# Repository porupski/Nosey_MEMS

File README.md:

# Nosey MEMS

**/ˈnɔɪzi miːmz/** — a fully open-source nasometer.

Nosey MEMS is a general purpose **mono MEMS microphone preamp**. It was specifically designed for integration with **Nosey** ([GitHub](https://github.com/phoneticslab/nosey) [Paper, IS25](https://www.isca-archive.org/interspeech_2025/dewhurst25_interspeech.pdf)) for acoustic nasalance measurements. A **stereo pair of boards** — one nasal, one oral — in the (not yet) adapted Nosey 3D-printed handle and baffle.

## What you get

- Open **KiCad 10.0** schematic, PCB and JLCPCB production files
- Small 25 × 50 mm board: NA-FFA381-A10-1 MEMS mic, OPA1652 balanced output, +48V phantom via XLR3
- Simple, low-cost (~€20 per built board as of June 2026), low-maintenance design
- Built for general purpose, aimed at phonetics, but the schematic/PCB can be adapted to any use

## Where to look

- **Documentation:** [porupski.github.io/Nosey_MEMS](https://porupski.github.io/Nosey_MEMS/)
- **`KiCad_files/`** — schematic, PCB layout, production `.zip`
- **`REW_files/`** — measured frequency response (Mk1 measurements, but the circuity is basically identical)
- **`docs/legacy_mk1/`** — the first, stereo Mk1 design (superseded)

## Status

In active development. The mono Mk2 replaces the earlier single-board stereo prototype, whose shared layout compromised acoustic separation between the nasal and oral channels.

## References

- Dewhurst et al. (2025). *Nosey: Open-source hardware for acoustic nasalance.* [arXiv:2505.23339](https://arxiv.org/pdf/2505.23339) · [IS25 PDF](https://www.isca-archive.org/interspeech_2025/dewhurst25_interspeech.pdf)

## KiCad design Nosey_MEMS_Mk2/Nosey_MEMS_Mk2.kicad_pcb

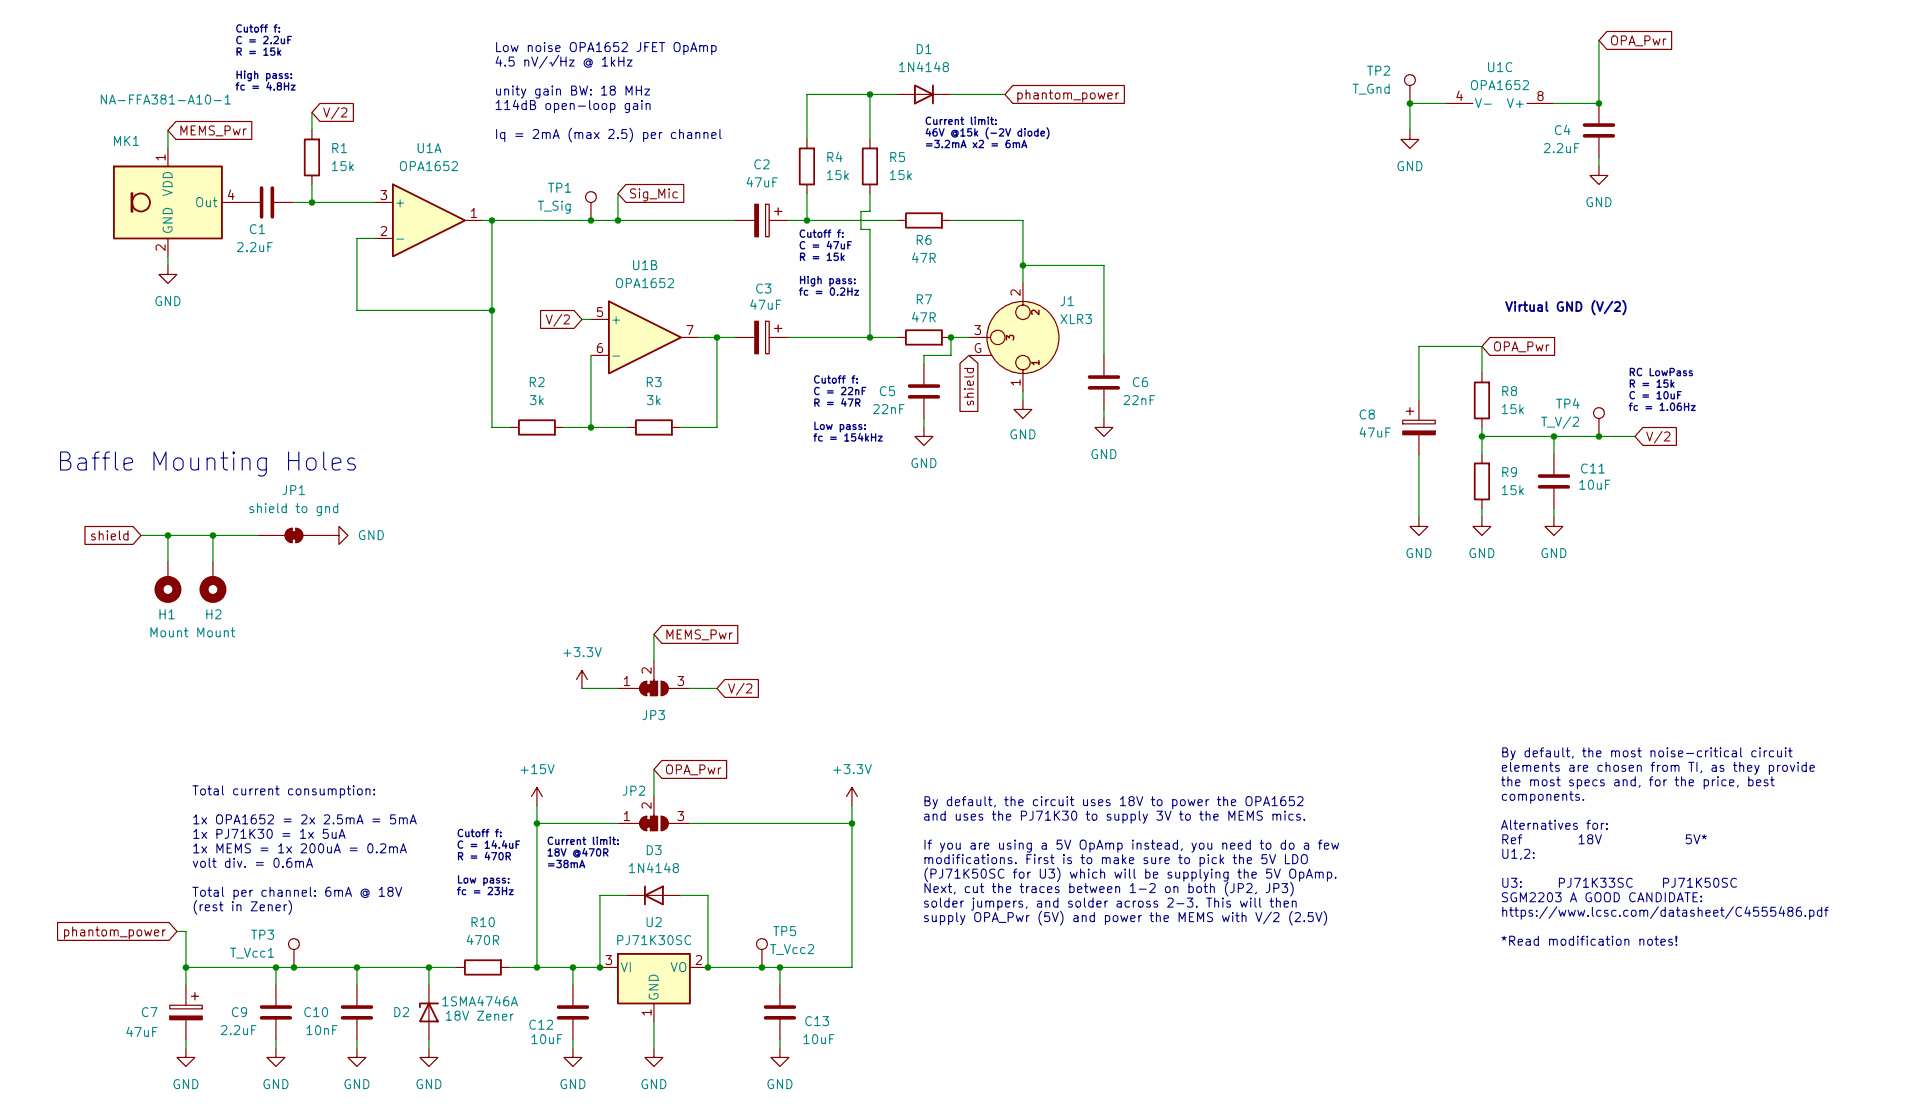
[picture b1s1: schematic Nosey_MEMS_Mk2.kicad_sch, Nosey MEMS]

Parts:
C1, C4, C9: 2.2uF; C_0805_2012Metric_Pad1.18x1.45mm_HandSolder
C2, C3, C7, C8: 47uF; CP_Elec_6.3x7.7
C5, C6: 22nF; C_0805_2012Metric_Pad1.18x1.45mm_HandSolder
C10: 10nF; C_0805_2012Metric_Pad1.18x1.45mm_HandSolder
C11, C12, C13: 10uF; C_0805_2012Metric_Pad1.18x1.45mm_HandSolder
D1, D3: 1N4148; D_SOD-323_HandSoldering
D2: 1SMA4746A; D_SMA_Handsoldering
H1, H2: Mount; MountingHole_3.2mm_M3_DIN965_Pad
J1: XLR3; Jack_XLR_Neutrik_NC3MAAH_Horizontal
JP1: shield to gnd; SolderJumper-2_P1.3mm_Bridged2Bar_RoundedPad1.0x1.5mm
JP2, JP3: SolderJumper_3_Open; SolderJumper-3_P1.3mm_Bridged12_RoundedPad1.0x1.5mm
MK1: NA-FFA381-A10-1; NA-FFA381-A10-1_MEMS_mic_analog_v1
R1, R4, R5, R8, R9: 15k; R_0805_2012Metric_Pad1.20x1.40mm_HandSolder
R2, R3: 3k; R_0805_2012Metric_Pad1.20x1.40mm_HandSolder
R6, R7: 47R; R_0805_2012Metric_Pad1.20x1.40mm_HandSolder
R10: 470R; R_0805_2012Metric_Pad1.20x1.40mm_HandSolder
TP1: T_Sig; TestPoint_Pad_D1.0mm
TP2: T_Gnd; TestPoint_Pad_2.5x2.5mm
TP3: T_Vcc1; TestPoint_Pad_2.5x2.5mm
TP4: T_V/2; TestPoint_Pad_2.5x2.5mm
TP5: T_Vcc2; TestPoint_Pad_2.5x2.5mm
U1: OPA1652; SOIC-8_3.9x4.9mm_P1.27mm
U2: PJ71K30SC; SOT-23

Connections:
+3.3V: C13.1, D3.2 (A), JP2.3 (B), JP3.1 (A), TP5.1 (1_1), U2.2 (VO)
+15V: C12.1, D3.1 (K), JP2.1 (A), R10.2, U2.3 (VI)
GND: C4.2, C5.2, C6.2, C7.2, C8.2, C9.2, C10.2, C11.2, C12.2, C13.2, D2.2 (A), J1.1, JP1.2 (B), MK1.2 (GND), MK1.3 (GND), R9.1, TP2.1 (1_1), U1.4 (V-), U2.1 (GND)
MEMS_Pwr: JP3.2 (C), MK1.1 (VDD)
unnamed: C2.1, R4.1, R6.1
unnamed: C3.1, R5.1, R7.1
unnamed: C3.2, R3.2, U1.7
unnamed: C5.1, J1.3, R7.2
unnamed: C6.1, J1.2, R6.2
unnamed: D1.2 (A), R4.2, R5.2
unnamed: C1.1, MK1.4 (Out)
unnamed: C1.2, R1.1, U1.3 (+)
unnamed: R2.2, R3.1, U1.6 (-)
OPA_Pwr: C4.1, C8.1, JP2.2 (C), R8.2, U1.8 (V+)
Sig_Mic: C2.2, R2.1, TP1.1 (1_1), U1.1, U1.2 (-)
V/2: C11.1, JP3.3 (B), R1.2, R8.1, R9.2, TP4.1 (1_1), U1.5 (+)
phantom_power: C7.1, C9.1, C10.1, D1.1 (K), D2.1 (K), R10.1, TP3.1 (1_1)
shield: H1.1 (1_1), H2.1 (1_1), J1.G, JP1.1 (A)

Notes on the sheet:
Current limit: 46V @15k (-2V diode) =3.2mA x2 = 6mA
RC LowPass R = 15k C = 10uF fc = 1.06Hz
Virtual GND (V/2)
Current limit: 18V @470R =38mA
Cutoff f: C = 2.2uF R = 15k High pass: fc = 4.8Hz
By default, the most noise-critical circuit elements are chosen from TI, as they provide the most specs and, for the price, best components. Alternatives for: Ref 18V 5V* U1,2: U3: PJ71K33SC PJ71K50SC SGM2203 A GOOD CANDIDATE: https://www.lcsc.com/datasheet/C4555486.pdf *Read modification notes!
Cutoff f: C = 22nF R = 47R Low pass: fc = 154kHz
By default, the circuit uses 18V to power the OPA1652 and uses the PJ71K30 to supply 3V to the MEMS mics. If you are using a 5V OpAmp instead, you need to do a few modifications. First is to make sure to pick the 5V LDO (PJ71K50SC for U3) which will be supplying the 5V OpAmp. Next, cut the traces b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
Total current consumption: 1x OPA1652 = 2x 2.5mA = 5mA 1x PJ71K30 = 1x 5uA 1x MEMS = 1x 200uA = 0.2mA volt div. = 0.6mA Total per channel: 6mA @ 18V (rest in Zener)
Cutoff f: C = 14.4uF R = 470R Low pass: fc = 23Hz
Baffle Mounting Holes
Cutoff f: C = 47uF R = 15k High pass: fc = 0.2Hz
Low noise OPA1652 JFET OpAmp 4.5 nV/√Hz @ 1kHz unity gain BW: 18 MHz 114dB open-loop gain Iq = 2mA (max 2.5) per channel

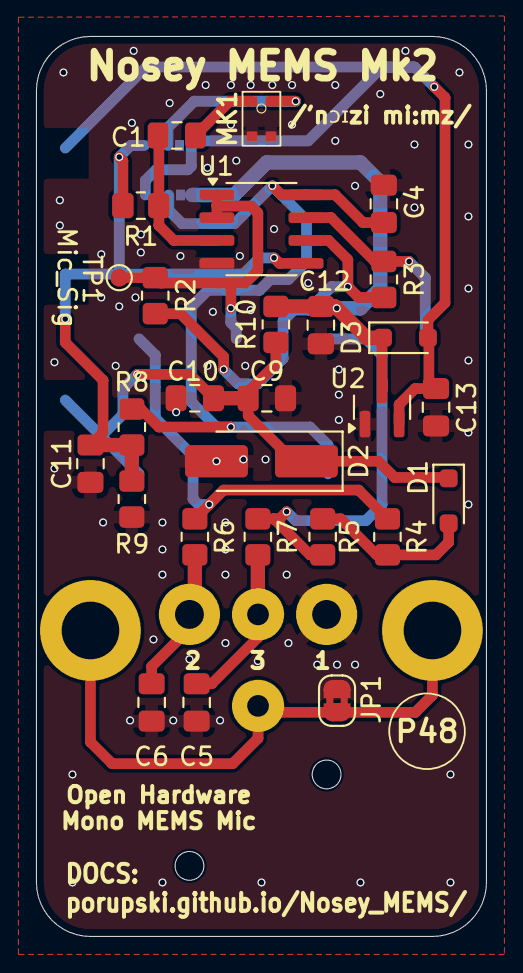
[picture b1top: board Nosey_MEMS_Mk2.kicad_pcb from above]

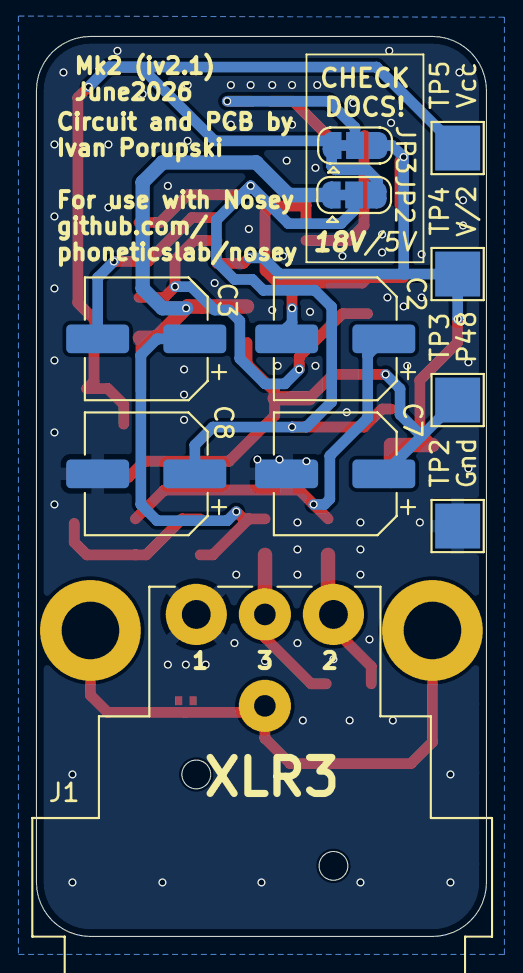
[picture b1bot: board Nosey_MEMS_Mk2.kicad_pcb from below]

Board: 2 copper layers, 25.0 x 50.0 mm, 40 parts (11 on the bottom side), 18 nets.

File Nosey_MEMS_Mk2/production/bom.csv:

Designator,Footprint,Quantity,Value,LCSC Part #
"C1, C4, C9",0805,3,2.2uF,
C10,0805,1,10nF,
"C11, C12, C13",0805,3,10uF,
"C2, C3, C7, C8",CP_Elec_6.3x7.7,4,47uF,
"C5, C6",0805,2,22nF,
"D1, D3",D_SOD-323_HandSoldering,2,1N4148,
D2,D_SMA_Handsoldering,1,1SMA4746A,
MK1,NA-FFA381-A10-1_MEMS_mic_analog_v1,1,NA-FFA381-A10-1,
"R1, R4, R5, R8, R9",0805,5,15k,
R10,0805,1,470R,
"R2, R3",0805,2,3k,
"R6, R7",0805,2,47R,
U1,SOIC-8_3.9x4.9mm_P1.27mm,1,OPA1652,
U2,SOT-23,1,PJ71K30SC,

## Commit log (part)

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2025-09-24 Create index.html
    First placeholder index.html
2025-09-24 Rename index.html to doc/index.html
2025-09-24 Rename index.html to index.html
2025-09-24 Updated the webpage with preliminary info.
2025-09-24 Images were important to include.
2025-09-24 Updated index with many a detail. New nicer image. Added style.css with dark/nightmode styling.
2025-09-26 Added encrypted .7z archives with KiCad files and production files. Not ready for public release just yet, but soon! Also did some edits on the index.html.
2025-09-26 Update README.md
    A more clear README plus a TODO roadmap.
2025-10-04 Update README.md
    Added Github Pages link
2025-10-04 Updated index with latest details and reworked the page formating further.
2025-10-04 Slight edits.
2025-10-05 Added the manufacture.html subpage with assembly information. Minor style and typo edits.
2025-10-06 Massive update to Manufacturing Guide. Finer details in index and style, added calibration.html starter page.
2025-10-06 Made navbar and sidebar separate. Updated minor things on pages. Started 3dprinting.html.
2025-10-07 Small revisions
2025-10-07 Sentence.
2025-10-07 Standardization updates to all sites. Added nasometry.html. Minor edits.
2025-10-07 Added debug prints to .js
2025-10-07 Added to Troubleshooting
2025-10-08 Changed h2 styling, expanded Troubleshooting
2025-10-08 Updated PCB image v2
2025-10-08 Slight changes
2025-11-01 Expanded on Manufacturing with newly received Nosey MEMS. Did the Calibration test and documented the steps and results.
2025-11-01 Added first public versions of the KiCad9 schematic and pcb board. Added first preliminary REW frequency sweep on both mics.
2025-11-01 Minor linking fixed.
2025-11-01 Small details fixed.
2025-11-01 Added hero shots of the finished device, front and back. Minor text editing.
2025-11-01 Small sidebar edits.
2025-11-22 Added to Calibration some Noise floor and Resonance responses. Included a stereo /ama/ /ana/ .wav file recorded with Nosey MEMS for first nasalance testing in practice.
2025-11-22 Added note
2025-11-23 Added Active Development page, updated some details.
2026-06-03 Added .gitignore
2026-06-03 Added first schematic and pcb for Mk2! Includes JLCPCB production files and STL model.
2026-06-03 TestPads causing issues for assembly ordering, better now.
2026-06-04 BIG UPDATE: Presenting Nosey MEMS Mk2! General purpose mono MEMS microphone + preamp, with nasometry in mind. More to come soon.
2026-06-04 Small fixes.
